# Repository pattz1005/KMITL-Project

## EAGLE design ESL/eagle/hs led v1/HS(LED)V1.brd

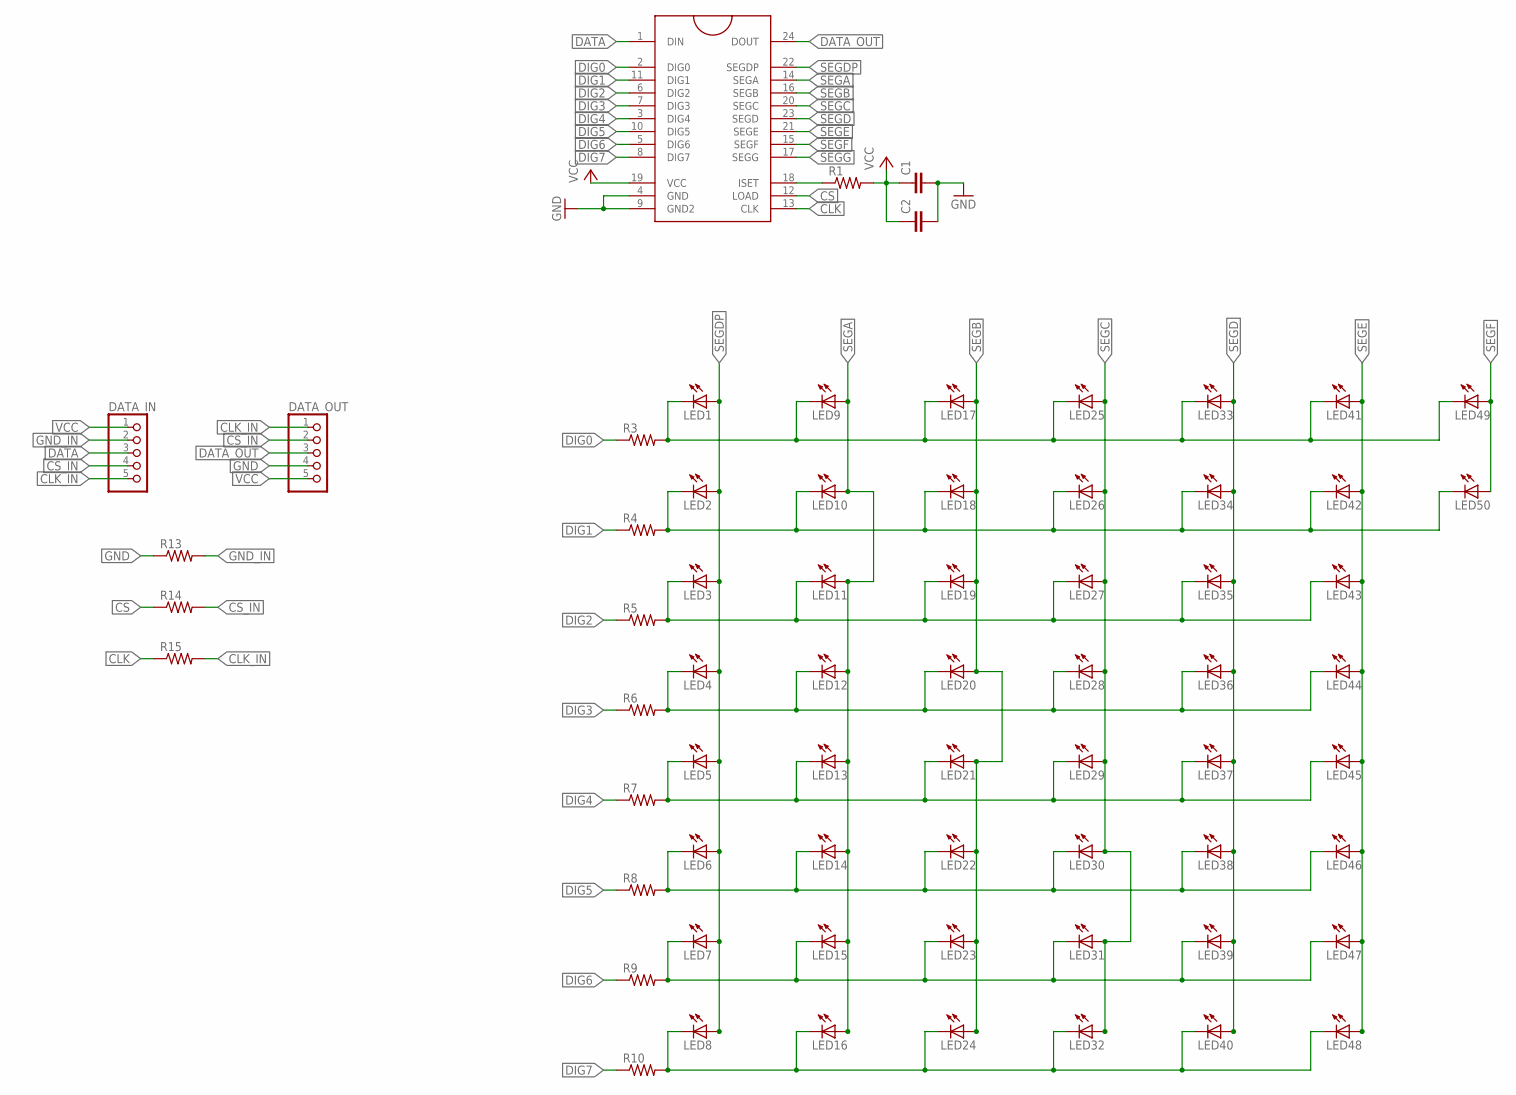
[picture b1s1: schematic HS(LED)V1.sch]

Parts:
C1, C2: C-EU025-024X044; C025-024X044
DATA_IN: PINHD-1X5/90; 1X05/90
DATA_OUT: PINHD-1X5/90; 1X05/90
LED1, LED2, LED3, LED4, LED5, LED6, LED7, LED8, LED9, LED10, LED11, LED12, LED13, LED14, LED15, LED16, LED17, LED18, LED19, LED20, LED21, LED22, LED23, LED24, LED25, LED26, LED27, LED28, LED29, LED30, LED31, LED32, LED33, LED34, LED35, LED36, LED37, LED38, LED39, LED40, LED41, LED42, LED43, LED44, LED45, LED46, LED47, LED48, LED49, LED50: LED3MM
R1, R3, R4, R5, R6, R7, R8, R9, R10, R13, R14, R15: R-US_0207/10; 0207/10
U$1: MAX7219DIP; DIL24

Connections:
CLK: R15.1, U$1.13 (CLK)
CLK_IN: DATA_IN.5, DATA_OUT.1, R15.2
CS: R14.1, U$1.12 (LOAD)
CS_IN: DATA_IN.4, DATA_OUT.2, R14.2
DATA: DATA_IN.3, U$1.1 (DIN)
DATA_OUT: DATA_OUT.3, U$1.24 (DOUT)
DIG0: R3.1, U$1.2 (DIG0)
DIG1: R4.1, U$1.11 (DIG1)
DIG2: R5.1, U$1.6 (DIG2)
DIG3: R6.1, U$1.7 (DIG3)
DIG4: R7.1, U$1.3 (DIG4)
DIG5: R8.1, U$1.10 (DIG5)
DIG6: R9.1, U$1.5 (DIG6)
DIG7: R10.1, U$1.8 (DIG7)
GND: C1.2, C2.2, DATA_OUT.4, R13.1, U$1.4 (GND), U$1.9 (GND2)
GND_IN: DATA_IN.2, R13.2
L0: LED1.K (C), LED9.K (C), LED17.K (C), LED25.K (C), LED33.K (C), LED41.K (C), LED49.K (C), R3.2
L1: LED2.K (C), LED10.K (C), LED18.K (C), LED26.K (C), LED34.K (C), LED42.K (C), LED50.K (C), R4.2
L2: LED3.K (C), LED11.K (C), LED19.K (C), LED27.K (C), LED35.K (C), LED43.K (C), R5.2
L3: LED4.K (C), LED12.K (C), LED20.K (C), LED28.K (C), LED36.K (C), LED44.K (C), R6.2
L4: LED5.K (C), LED13.K (C), LED21.K (C), LED29.K (C), LED37.K (C), LED45.K (C), R7.2
L5: LED6.K (C), LED14.K (C), LED22.K (C), LED30.K (C), LED38.K (C), LED46.K (C), R8.2
L6: LED7.K (C), LED15.K (C), LED23.K (C), LED31.K (C), LED39.K (C), LED47.K (C), R9.2
L7: LED8.K (C), LED16.K (C), LED24.K (C), LED32.K (C), LED40.K (C), LED48.K (C), R10.2
unnamed: R1.1, U$1.18 (ISET)
SEGA: LED9.A, LED10.A, LED11.A, LED12.A, LED13.A, LED14.A, LED15.A, LED16.A, U$1.14 (SEGA)
SEGB: LED17.A, LED18.A, LED19.A, LED20.A, LED21.A, LED22.A, LED23.A, LED24.A, U$1.16 (SEGB)
SEGC: LED25.A, LED26.A, LED27.A, LED28.A, LED29.A, LED30.A, LED31.A, LED32.A, U$1.20 (SEGC)
SEGD: LED33.A, LED34.A, LED35.A, LED36.A, LED37.A, LED38.A, LED39.A, LED40.A, U$1.23 (SEGD)
SEGDP: LED1.A, LED2.A, LED3.A, LED4.A, LED5.A, LED6.A, LED7.A, LED8.A, U$1.22 (SEGDP)
SEGE: LED41.A, LED42.A, LED43.A, LED44.A, LED45.A, LED46.A, LED47.A, LED48.A, U$1.21 (SEGE)
SEGF: LED49.A, LED50.A, U$1.15 (SEGF)
SEGG: U$1.17 (SEGG)
VCC: C1.1, C2.1, DATA_IN.1, DATA_OUT.5, R1.2, U$1.19 (VCC)

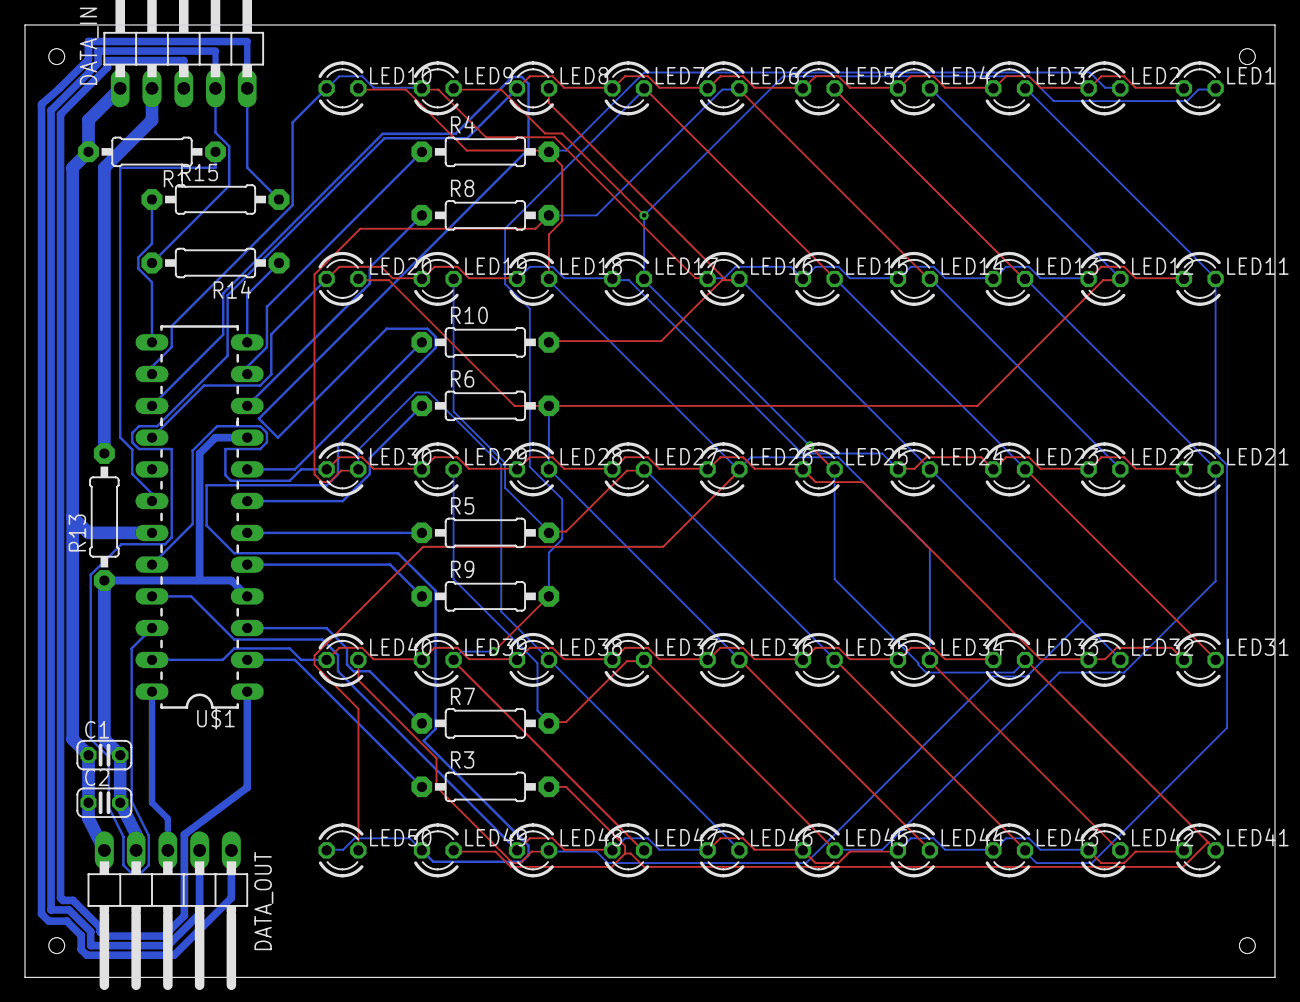
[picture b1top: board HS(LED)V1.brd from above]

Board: 2 copper layers, 100.0 x 76.2 mm, 67 parts (0 on the bottom side), 33 nets.

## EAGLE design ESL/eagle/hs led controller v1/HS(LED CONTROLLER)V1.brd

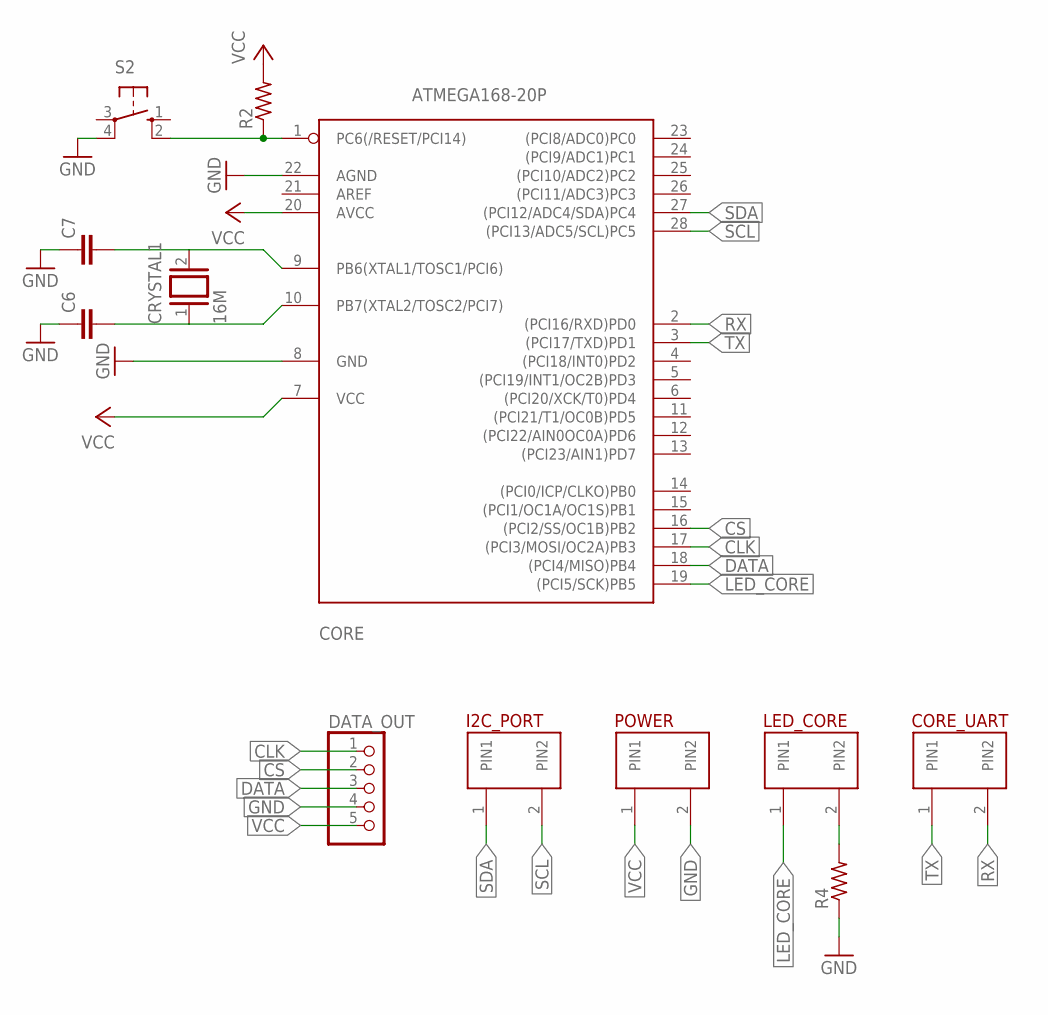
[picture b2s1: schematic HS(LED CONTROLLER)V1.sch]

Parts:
C6, C7: C-EU025-024X044; C025-024X044
CORE: ATMEGA168-20P; DIL28-3
CORE_UART: 7325; 2.54MM
CRYSTAL1: 16M; QS
DATA_OUT: PINHD-1X5/90; 1X05/90
I2C_PORT: 7325; 2.54MM
LED_CORE: 7325; 2.54MM
POWER: 7325; 2.54MM
R2, R4: R-US_0207/10; 0207/10
S2: 10-XX; B3F-10XX

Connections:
CLK: CORE.17 ((PCI3/MOSI/OC2A)PB3), DATA_OUT.1
CS: CORE.16 ((PCI2/SS/OC1B)PB2), DATA_OUT.2
DATA: CORE.18 ((PCI4/MISO)PB4), DATA_OUT.3
GND: C6.1, C7.1, CORE.8 (GND), CORE.22 (AGND), DATA_OUT.4, POWER.2 (PIN2), R4.1, S2.4 (P1)
LED_CORE: CORE.19 ((PCI5/SCK)PB5), LED_CORE.1 (PIN1)
unnamed: LED_CORE.2 (PIN2), R4.2
unnamed: C7.2, CORE.9 (PB6(XTAL1/TOSC1/PCI6)), CRYSTAL1.2
unnamed: C6.2, CORE.10 (PB7(XTAL2/TOSC2/PCI7)), CRYSTAL1.1
unnamed: CORE.1 (PC6(/RESET/PCI14)), R2.1, S2.2 (S1)
RX: CORE.2 ((PCI16/RXD)PD0), CORE_UART.2 (PIN2)
SCL: CORE.28 ((PCI13/ADC5/SCL)PC5), I2C_PORT.2 (PIN2)
SDA: CORE.27 ((PCI12/ADC4/SDA)PC4), I2C_PORT.1 (PIN1)
TX: CORE.3 ((PCI17/TXD)PD1), CORE_UART.1 (PIN1)
VCC: CORE.7 (VCC), CORE.20 (AVCC), DATA_OUT.5, POWER.1 (PIN1), R2.2

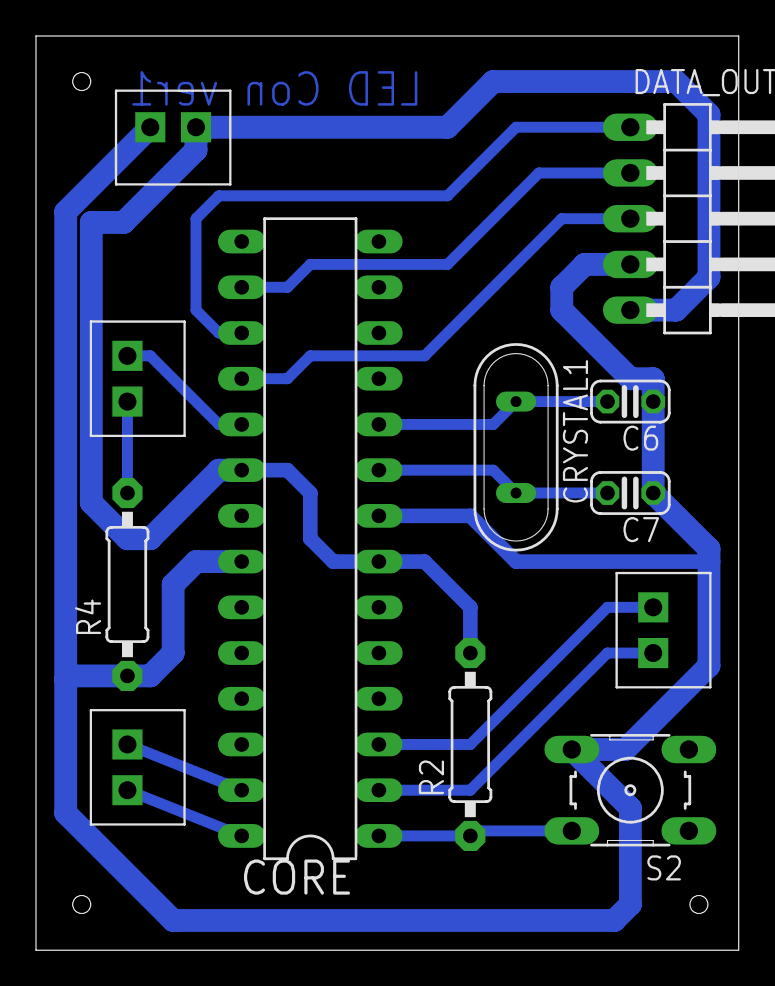
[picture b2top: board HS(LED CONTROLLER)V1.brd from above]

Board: 2 copper layers, 39.0 x 50.8 mm, 12 parts (0 on the bottom side), 14 nets.

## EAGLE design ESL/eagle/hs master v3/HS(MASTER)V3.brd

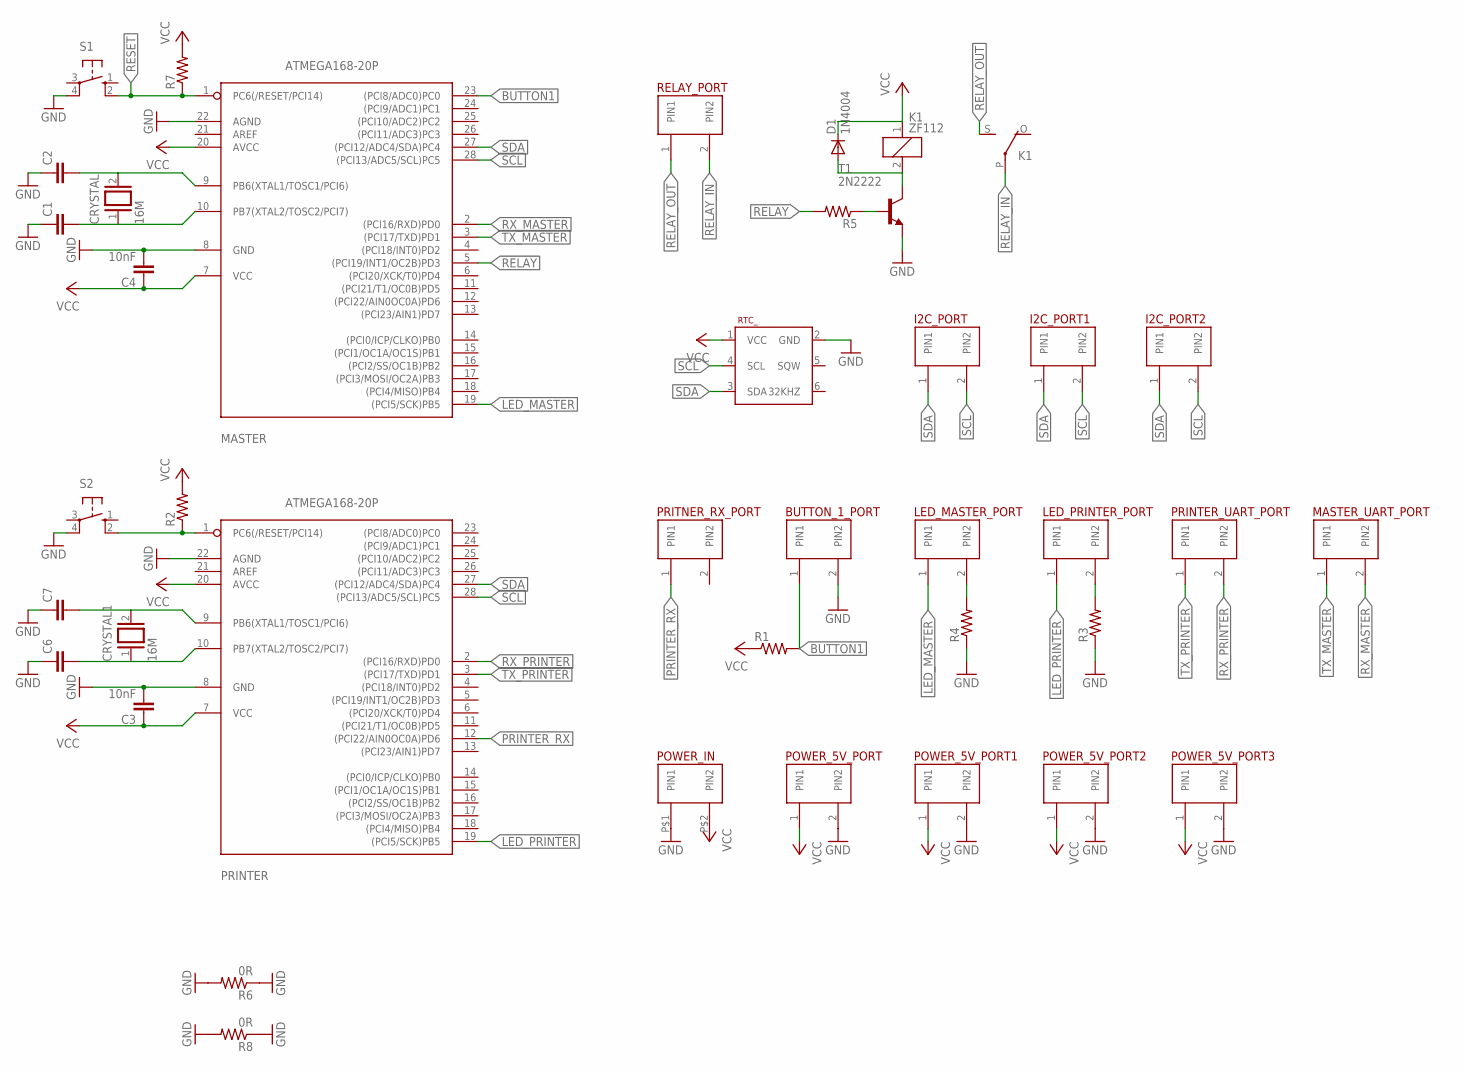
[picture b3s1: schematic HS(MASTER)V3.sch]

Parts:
BUTTON_1_PORT: 7325; 2.54MM
C1, C2, C6, C7: C-EU025-024X044; C025-024X044
C3, C4: 10nF; C5B2.5
CRYSTAL, CRYSTAL1: 16M; QS
D1: 1N4004; DO41-10
I2C_PORT, I2C_PORT1, I2C_PORT2: 7325; 2.54MM
K1: ZF112
LED_MASTER_PORT: 7325; 2.54MM
LED_PRINTER_PORT: 7325; 2.54MM
MASTER: ATMEGA168-20P; DIL28-3
MASTER_UART_PORT: 7325; 2.54MM
POWER_5V_PORT, POWER_5V_PORT1, POWER_5V_PORT2, POWER_5V_PORT3: 7325; 2.54MM
POWER_IN: 4396; 4MM
PRINTER: ATMEGA168-20P; DIL28-3
PRINTER_UART_PORT: 7325; 2.54MM
PRITNER_RX_PORT: 7325; 2.54MM
R1, R2, R3, R4, R5, R7: R-US_0207/10; 0207/10
R6, R8: 0R; 0207/10
RELAY_PORT: 7325; 2.54MM
RTC_: RTC_DS3231_6_PIN
S1, S2: 10-XX; B3F-10XX
T1: 2N2222; TO92-EBC-OVAL

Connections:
BUTTON1: BUTTON_1_PORT.1 (PIN1), MASTER.23 ((PCI8/ADC0)PC0), R1.2
GND: BUTTON_1_PORT.2 (PIN2), C1.1, C2.1, C3.2, C4.2, C6.1, C7.1, MASTER.8 (GND), MASTER.22 (AGND), POWER_5V_PORT.2 (PIN2), POWER_5V_PORT1.2 (PIN2), POWER_5V_PORT2.2 (PIN2), POWER_5V_PORT3.2 (PIN2), POWER_IN.P$1 (PIN1), PRINTER.8 (GND), PRINTER.22 (AGND), R3.1, R4.1, R6.1, R6.2, R8.1, R8.2, RTC_.2 (GND), S1.4 (P1), S2.4 (P1), T1.E
LED_MASTER: LED_MASTER_PORT.1 (PIN1), MASTER.19 ((PCI5/SCK)PB5)
LED_PRINTER: LED_PRINTER_PORT.1 (PIN1), PRINTER.19 ((PCI5/SCK)PB5)
unnamed: C2.2, CRYSTAL.2, MASTER.9 (PB6(XTAL1/TOSC1/PCI6))
unnamed: C1.2, CRYSTAL.1, MASTER.10 (PB7(XTAL2/TOSC2/PCI7))
unnamed: D1.A, K1.2, T1.C
unnamed: LED_MASTER_PORT.2 (PIN2), R4.2
unnamed: C7.2, CRYSTAL1.2, PRINTER.9 (PB6(XTAL1/TOSC1/PCI6))
unnamed: C6.2, CRYSTAL1.1, PRINTER.10 (PB7(XTAL2/TOSC2/PCI7))
unnamed: PRINTER.1 (PC6(/RESET/PCI14)), R2.1, S2.2 (S1)
unnamed: LED_PRINTER_PORT.2 (PIN2), R3.2
unnamed: R5.1, T1.B
PRINTER_RX: PRINTER.12 ((PCI22/AIN0OC0A)PD6), PRITNER_RX_PORT.1 (PIN1)
RELAY: MASTER.5 ((PCI19/INT1/OC2B)PD3), R5.2
RELAY_IN: K1.P, RELAY_PORT.2 (PIN2)
RELAY_OUT: K1.S, RELAY_PORT.1 (PIN1)
RESET: MASTER.1 (PC6(/RESET/PCI14)), R7.1, S1.2 (S1)
RX_MASTER: MASTER.2 ((PCI16/RXD)PD0), MASTER_UART_PORT.2 (PIN2)
RX_PRINTER: PRINTER.2 ((PCI16/RXD)PD0), PRINTER_UART_PORT.2 (PIN2)
SCL: I2C_PORT.2 (PIN2), I2C_PORT1.2 (PIN2), I2C_PORT2.2 (PIN2), MASTER.28 ((PCI13/ADC5/SCL)PC5), PRINTER.28 ((PCI13/ADC5/SCL)PC5), RTC_.4 (SCL)
SDA: I2C_PORT.1 (PIN1), I2C_PORT1.1 (PIN1), I2C_PORT2.1 (PIN1), MASTER.27 ((PCI12/ADC4/SDA)PC4), PRINTER.27 ((PCI12/ADC4/SDA)PC4), RTC_.3 (SDA)
TX_MASTER: MASTER.3 ((PCI17/TXD)PD1), MASTER_UART_PORT.1 (PIN1)
TX_PRINTER: PRINTER.3 ((PCI17/TXD)PD1), PRINTER_UART_PORT.1 (PIN1)
VCC: C3.1, C4.1, D1.C, K1.1, MASTER.7 (VCC), MASTER.20 (AVCC), POWER_5V_PORT.1 (PIN1), POWER_5V_PORT1.1 (PIN1), POWER_5V_PORT2.1 (PIN1), POWER_5V_PORT3.1 (PIN1), POWER_IN.P$2 (PIN2), PRINTER.7 (VCC), PRINTER.20 (AVCC), R1.1, R2.2, R7.2, RTC_.1 (VCC)

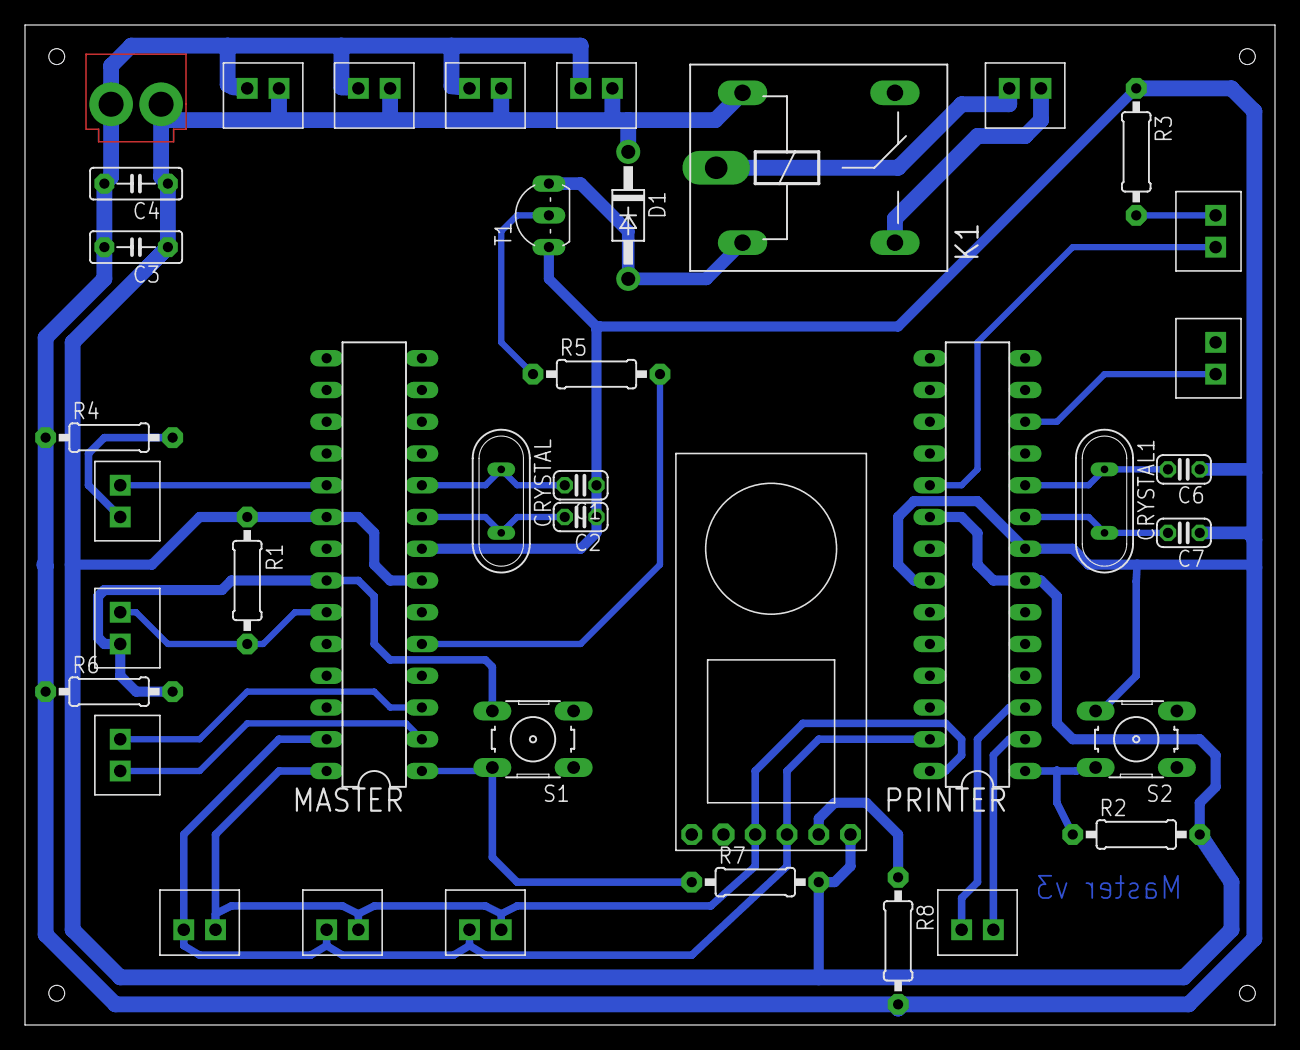
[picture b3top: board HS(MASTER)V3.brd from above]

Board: 2 copper layers, 100.0 x 80.0 mm, 39 parts (0 on the bottom side), 25 nets.

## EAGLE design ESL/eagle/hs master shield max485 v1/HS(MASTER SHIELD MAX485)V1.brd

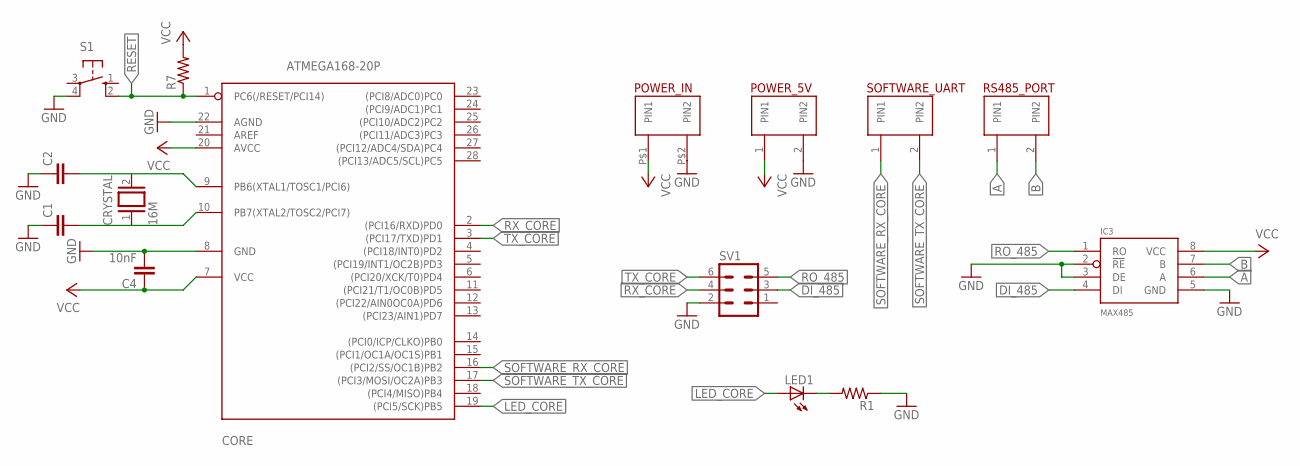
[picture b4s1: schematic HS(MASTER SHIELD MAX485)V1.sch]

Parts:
C1, C2: C-EU025-024X044; C025-024X044
C4: 10nF; C5B2.5
CORE: ATMEGA168-20P; DIL28-3
CRYSTAL: 16M; QS
IC3: MAX485; DIP8
LED1: LED3MM
POWER_5V: 7325; 2.54MM
POWER_IN: 4396; 4MM
R1, R7: R-US_0207/10; 0207/10
RS485_PORT: 7325; 2.54MM
S1: 10-XX; B3F-10XX
SOFTWARE_UART: 7325; 2.54MM
SV1: MA03-2

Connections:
A: IC3.6 (A), RS485_PORT.1 (PIN1)
B: IC3.7 (B), RS485_PORT.2 (PIN2)
DI_485: IC3.4 (DI), SV1.3
GND: C1.1, C2.1, C4.2, CORE.8 (GND), CORE.22 (AGND), IC3.2 (!RE), IC3.3 (DE), IC3.5 (GND), POWER_5V.2 (PIN2), POWER_IN.P$2 (PIN2), R1.1, S1.4 (P1), SV1.2
LED_CORE: CORE.19 ((PCI5/SCK)PB5), LED1.A
unnamed: C2.2, CORE.9 (PB6(XTAL1/TOSC1/PCI6)), CRYSTAL.2
unnamed: C1.2, CORE.10 (PB7(XTAL2/TOSC2/PCI7)), CRYSTAL.1
unnamed: LED1.K (C), R1.2
RESET: CORE.1 (PC6(/RESET/PCI14)), R7.1, S1.2 (S1)
RO_485: IC3.1 (RO), SV1.5
RX_CORE: CORE.2 ((PCI16/RXD)PD0), SV1.4
SOFTWARE_RX_CORE: CORE.16 ((PCI2/SS/OC1B)PB2), SOFTWARE_UART.1 (PIN1)
SOFTWARE_TX_CORE: CORE.17 ((PCI3/MOSI/OC2A)PB3), SOFTWARE_UART.2 (PIN2)
TX_CORE: CORE.3 ((PCI17/TXD)PD1), SV1.6
VCC: C4.1, CORE.7 (VCC), CORE.20 (AVCC), IC3.8 (VCC), POWER_5V.1 (PIN1), POWER_IN.P$1 (PIN1), R7.2

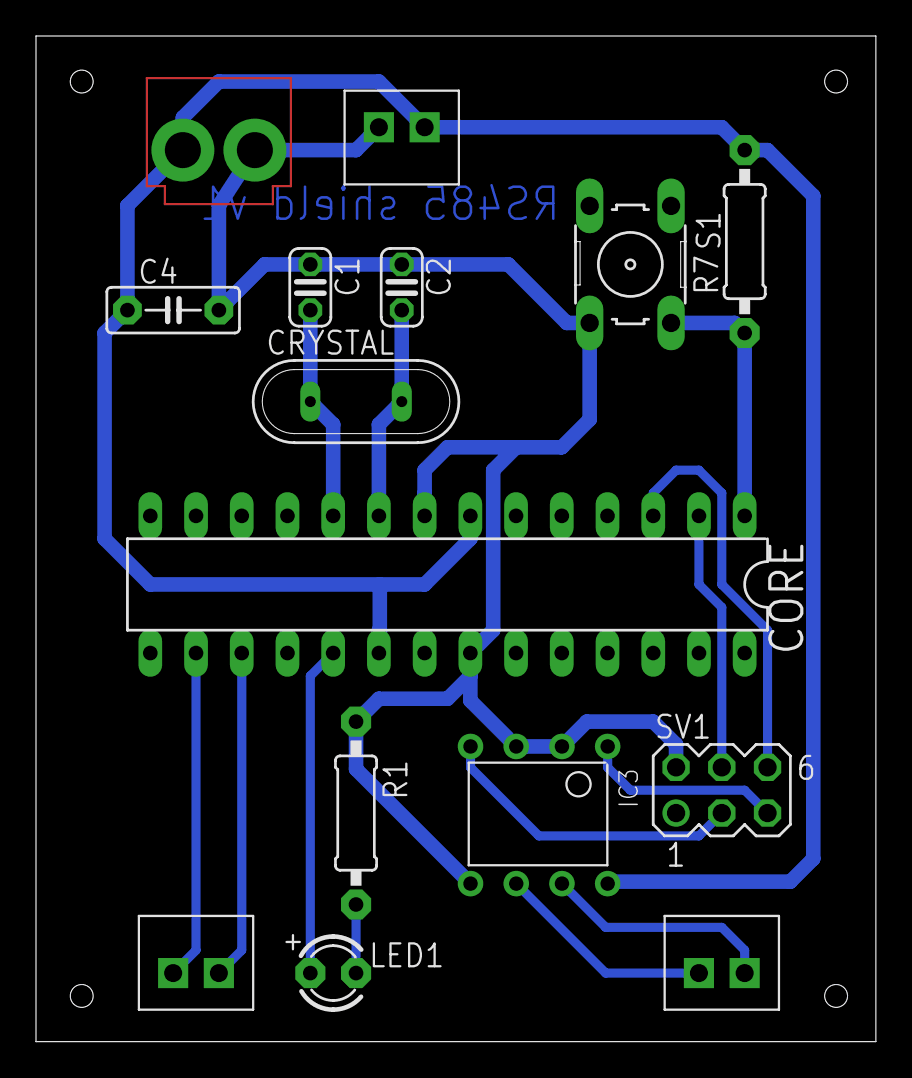
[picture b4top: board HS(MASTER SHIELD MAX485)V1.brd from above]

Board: 2 copper layers, 46.7 x 55.9 mm, 15 parts (0 on the bottom side), 15 nets.

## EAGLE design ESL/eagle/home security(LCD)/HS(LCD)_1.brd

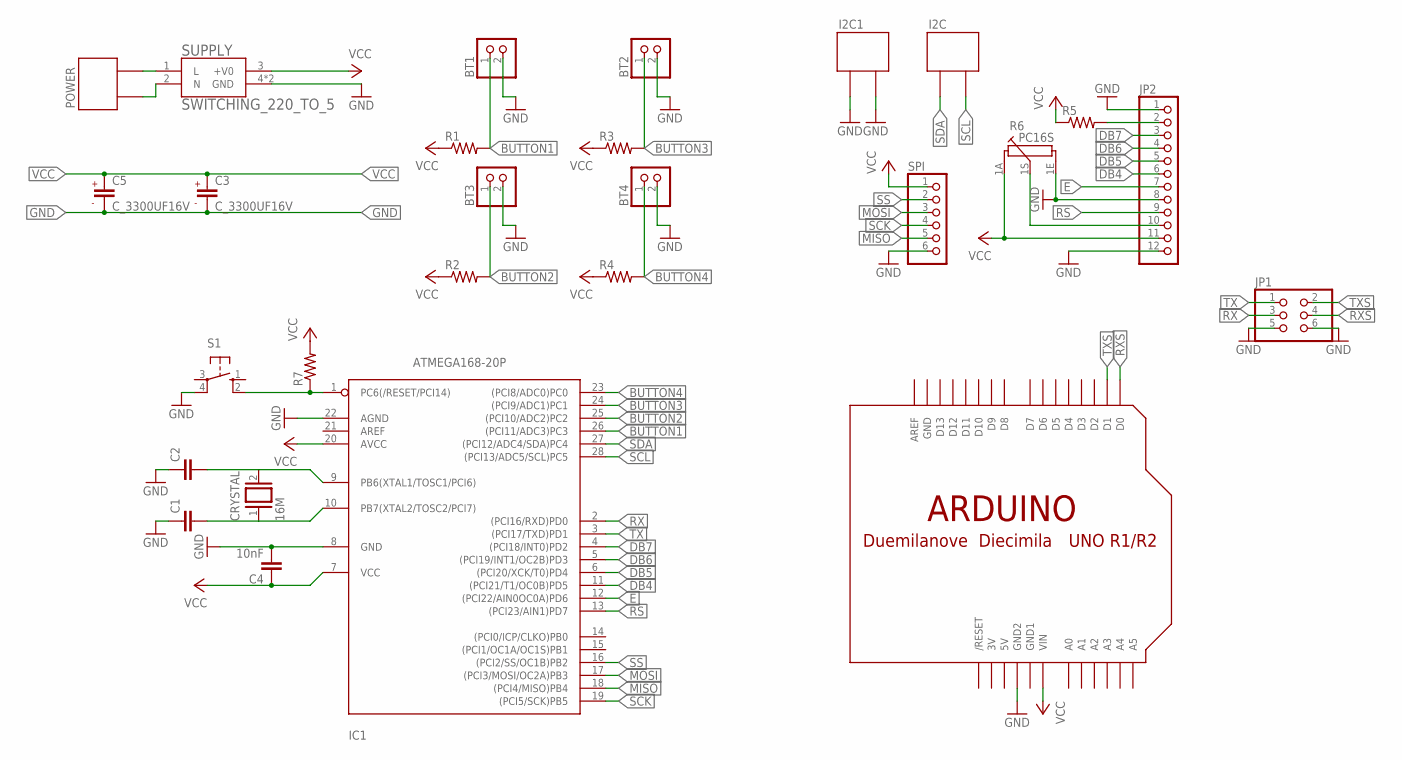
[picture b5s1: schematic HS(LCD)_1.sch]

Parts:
BT1, BT2, BT3, BT4: PINHD-1X2; 1X02
C1, C2: C-EU025-024X044; C025-024X044
C3, C5: C_3300UF16V; RADIAL_3300UF16V
C4: 10nF; C5B2.5
CRYSTAL: 16M; QS
I2C, I2C1: 2PIN_TERMINAL_BLOCK
IC1: ATMEGA168-20P; DIL28-3
JP1: PINHD-2X3; 2X03
JP2: PINHD-1X12; 1X12
POWER: 2PIN_TERMINAL_BLOCK
R1, R2, R3, R4, R5, R7: R-US_0204/7; 0204/7
R6: PC16S
S1: 10-XX; B3F-10XX
SPI: PINHD-1X6; 1X06
SUPPLY: SWITCHING_220_TO_5; SUPPLY_220V_5V
U$1: ARDUINO-NOHOLE

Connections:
3V: U$1.3V
5V: U$1.5V
BUTTON1: BT1.1, IC1.26 ((PCI11/ADC3)PC3), R1.2
BUTTON2: BT3.1, IC1.25 ((PCI10/ADC2)PC2), R2.2
BUTTON3: BT2.1, IC1.24 ((PCI9/ADC1)PC1), R3.2
BUTTON4: BT4.1, IC1.23 ((PCI8/ADC0)PC0), R4.2
DB4: IC1.11 ((PCI21/T1/OC0B)PD5), JP2.6
DB5: IC1.6 ((PCI20/XCK/T0)PD4), JP2.5
DB6: IC1.5 ((PCI19/INT1/OC2B)PD3), JP2.4
DB7: IC1.4 ((PCI18/INT0)PD2), JP2.3
E: IC1.12 ((PCI22/AIN0OC0A)PD6), JP2.7
GND: BT1.2, BT2.2, BT3.2, BT4.2, C1.1, C2.1, C3.1 (GND), C4.2, C5.1 (GND), I2C1.P$1, I2C1.P$2, IC1.8 (GND), IC1.22 (AGND), JP1.5, JP1.6, JP2.1, JP2.8, JP2.12, R6.1E, S1.4 (P1), SPI.6, SUPPLY.4 (GND), SUPPLY.5 (GND), U$1.GND, U$1.GND2
GND1: U$1.GND1
LEDP: JP2.2, R5.2
MISO: IC1.18 ((PCI4/MISO)PB4), SPI.5
MOSI: IC1.17 ((PCI3/MOSI/OC2A)PB3), SPI.3
unnamed: C2.2, CRYSTAL.2, IC1.9 (PB6(XTAL1/TOSC1/PCI6))
unnamed: C1.2, CRYSTAL.1, IC1.10 (PB7(XTAL2/TOSC2/PCI7))
unnamed: POWER.P$2, SUPPLY.1 (L)
unnamed: POWER.P$1, SUPPLY.2 (N)
unnamed: IC1.1 (PC6(/RESET/PCI14)), R7.1, S1.2 (S1)
RS: IC1.13 ((PCI23/AIN1)PD7), JP2.9
RX: IC1.2 ((PCI16/RXD)PD0), JP1.3
RXS: JP1.4, U$1.D0
SCK: IC1.19 ((PCI5/SCK)PB5), SPI.4
SCL: I2C.P$2, IC1.28 ((PCI13/ADC5/SCL)PC5)
SDA: I2C.P$1, IC1.27 ((PCI12/ADC4/SDA)PC4)
SS: IC1.16 ((PCI2/SS/OC1B)PB2), SPI.2
TX: IC1.3 ((PCI17/TXD)PD1), JP1.1
TXS: JP1.2, U$1.D1
V0: JP2.10, R6.1S
VCC: C3.2 (VCC), C4.1, C5.2 (VCC), IC1.7 (VCC), IC1.20 (AVCC), JP2.11, R1.1, R2.1, R3.1, R4.1, R5.1, R6.1A, R7.2, SPI.1, SUPPLY.3 (+V0), U$1.VIN

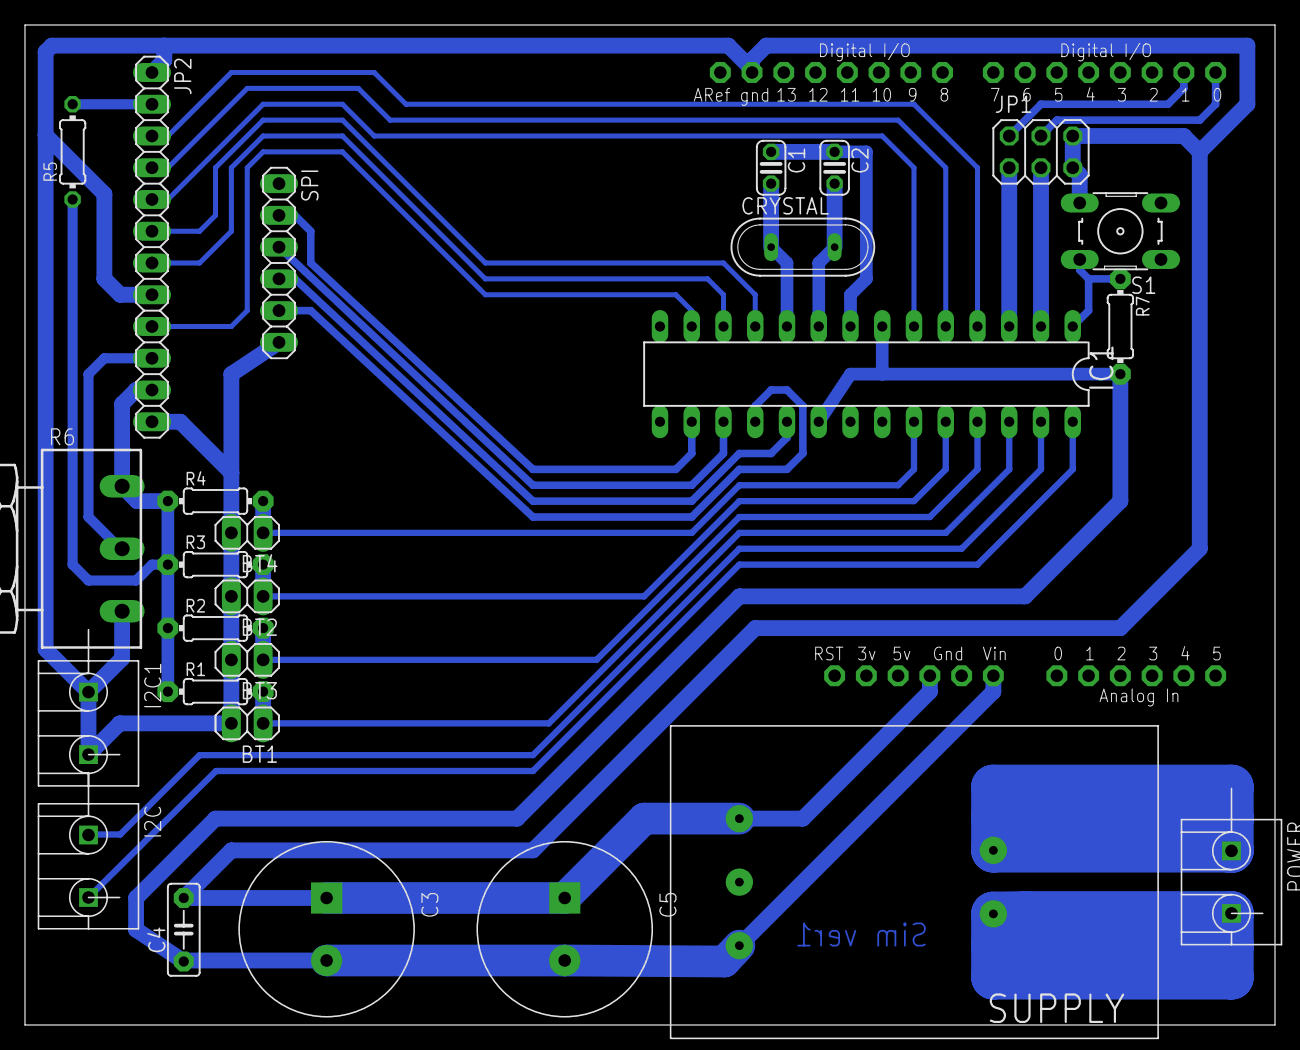
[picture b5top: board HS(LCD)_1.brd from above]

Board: 2 copper layers, 100.0 x 80.0 mm, 27 parts (0 on the bottom side), 29 nets.

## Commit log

2020-03-10 Create keep
2020-03-10 ESL and SE commit
2020-03-10 ESL commit
2020-03-10 update esl
